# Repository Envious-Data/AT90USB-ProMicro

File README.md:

# AT90USB-ProMicro
 A AT90USB Pro Micro sized board.

I quickly threw this together on a whim because why not, it needs a bit of tweaking to perfectly fit a pro micro footprint but in theory this should work if you get all the parts and solder it on.

I am also thinking about making a Pro Micro to RPI Pico adapter of some sort since pro micro sized boards are both popular and widely avaliable.

This has been nicknamed the Envi-C where the C stands for Cat.

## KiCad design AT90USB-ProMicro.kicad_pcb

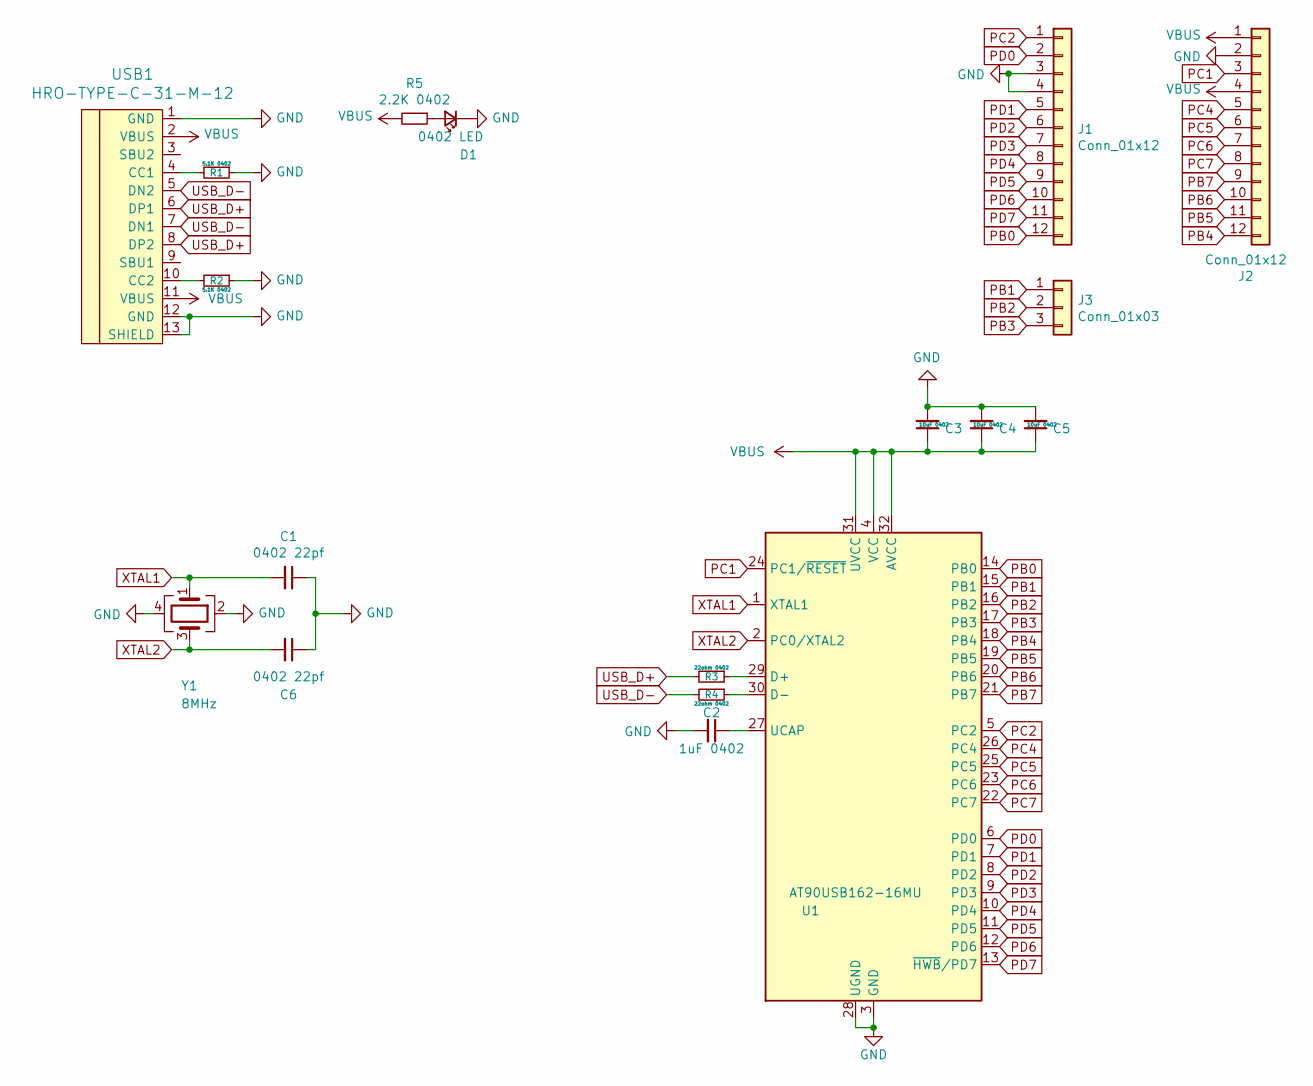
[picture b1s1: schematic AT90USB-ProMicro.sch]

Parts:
C1, C6: 0402 22pf; C_0402_1005Metric
C2: 1uF 0402; C_0402_1005Metric
C3, C4, C5: 10uF 0402; C_0402_1005Metric
D1: 0402 LED; LED_0402_1005Metric
J1, J2: Conn_01x12; PinHeader_1x12_P2.54mm_Vertical
J3: Conn_01x03; PinHeader_1x03_P2.54mm_Vertical
R1, R2: 5.1K 0402; R_0402_1005Metric
R3, R4: 22ohm 0402; R_0402_1005Metric
R5: 2.2K 0402; R_0402_1005Metric
U1: AT90USB162-16MU; QFN-32-1EP_5x5mm_P0.5mm_EP3.6x3.6mm
USB1: HRO-TYPE-C-31-M-12; HRO-TYPE-C-31-M-12-Assembly
Y1: 8MHz; Crystal_SMD_3225-4Pin_3.2x2.5mm

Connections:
GND: C1.1, C2.2, C3.2, C4.2, C5.2, C6.1, D1.1 (K), J1.3, J1.4, J2.2, R1.1, R2.1, U1.3 (GND), U1.28 (UGND), U1.33 (GND), USB1.1 (GND), USB1.12 (GND), USB1.13 (SHIELD), Y1.2, Y1.4
unnamed: C2.1, U1.27 (UCAP)
unnamed: D1.2 (A), R5.1
unnamed: R1.2, USB1.4 (CC1)
unnamed: R2.2, USB1.10 (CC2)
unnamed: R3.1, U1.29 (D+)
unnamed: R4.1, U1.30 (D-)
PB0: J1.12, U1.14 (PB0)
PB1: J3.1, U1.15 (PB1)
PB2: J3.2, U1.16 (PB2)
PB3: J3.3, U1.17 (PB3)
PB4: J2.12, U1.18 (PB4)
PB5: J2.11, U1.19 (PB5)
PB6: J2.10, U1.20 (PB6)
PB7: J2.9, U1.21 (PB7)
PC1: J2.3, U1.24 (PC1/~RESET)
PC2: J1.1, U1.5 (PC2)
PC4: J2.5, U1.26 (PC4)
PC5: J2.6, U1.25 (PC5)
PC6: J2.7, U1.23 (PC6)
PC7: J2.8, U1.22 (PC7)
PD0: J1.2, U1.6 (PD0)
PD1: J1.5, U1.7 (PD1)
PD2: J1.6, U1.8 (PD2)
PD3: J1.7, U1.9 (PD3)
PD4: J1.8, U1.10 (PD4)
PD5: J1.9, U1.11 (PD5)
PD6: J1.10, U1.12 (PD6)
PD7: J1.11, U1.13 (~HWB~/PD7)
USB_D+: R3.2, USB1.6 (DP1), USB1.8 (DP2)
USB_D-: R4.2, USB1.5 (DN2), USB1.7 (DN1)
VBUS: C3.1, C4.1, C5.1, J2.1, J2.4, R5.2, U1.4 (VCC), U1.31 (UVCC), U1.32 (AVCC), USB1.2 (VBUS), USB1.11 (VBUS)
XTAL1: C1.2, U1.1 (XTAL1), Y1.1
XTAL2: C6.2, U1.2 (PC0/XTAL2), Y1.3

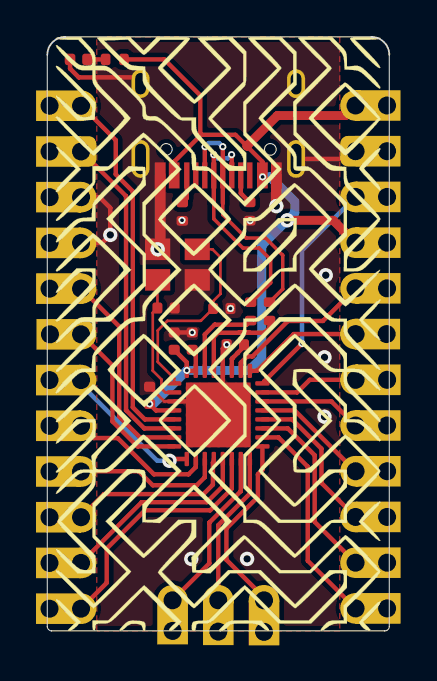
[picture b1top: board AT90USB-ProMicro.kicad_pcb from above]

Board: 2 copper layers, 19.0 x 33.0 mm, 18 parts (1 on the bottom side), 34 nets.

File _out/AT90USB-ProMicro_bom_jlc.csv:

"Comment","Designator","Footprint","LCSC Part #"
"0402 22pf","C1,C6","C_0402_1005Metric","no_part_number"
"1uF 0402","C2","C_0402_1005Metric","no_part_number"
"10uF 0402","C3,C4,C5","C_0402_1005Metric","no_part_number"
"0402 LED","D1","LED_0402_1005Metric","no_part_number"
"Conn_01x12","J1,J2","PinHeader_1x12_P2.54mm_Vertical","no_part_number"
"Conn_01x03","J3","PinHeader_1x03_P2.54mm_Vertical","no_part_number"
"5.1K 0402","R2,R1","R_0402_1005Metric","no_part_number"
"22ohm 0402","R3,R4","R_0402_1005Metric","no_part_number"
"2.2K 0402","R5","R_0402_1005Metric","no_part_number"
"AT90USB162-16MU","U1","QFN-32-1EP_5x5mm_P0.5mm_EP3.6x3.6mm","no_part_number"
"HRO-TYPE-C-31-M-12","USB1","HRO-TYPE-C-31-M-12-Assembly","no_part_number"
"8MHz","Y1","Crystal_SMD_3225-4Pin_3.2x2.5mm","no_part_number"

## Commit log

2021-08-04 updated readme + aded image
2021-08-05 Corrected alignment to match the pro micro properly.
2021-08-05 broke out spare MCU pins to a header.
2021-08-05 swapped header to be correct way. may need to re-align it to fit other pro-micro like boards.
2021-08-05 Added some silkscreen notes and realigned some capacitors, resistors and usb traces
2021-08-06 added a couple more decoupling capacitors, one for 3.3V LDO and one for the clock
2021-08-06 changed part description in schematic
2021-08-15 Corrected errors as per DRC
2021-08-16 changed oscillator for crystal, 3225 gnd on 2 and 4.
2021-09-03 Added a Kiwi pattern on both sides of the board to make it look "Pretty"
2021-09-04 Changed pattern out for a geo graphic looking one, much nicer i think.
2021-09-04 upload the base file I used for the silkscreen pattern.
2021-09-04 Generated some Gerbers.
2021-09-04 added castellations on all pins
2021-09-04 correct pin hole placement and castellations
2021-09-04 some small tweaks and corrections to mute DRC errors
2021-09-04 adjusted panel and mousebites
2021-09-04 Rounded the corners of the PCB.
2021-09-04 updated image as there have been quite some changes to the board.
2021-09-04 updated the panelize bash script to work under WSL.
2021-09-05 tiny bit of housekeeping, i.e cleaning up doubled tracks and what not.
2022-01-18 updated git-ignore
